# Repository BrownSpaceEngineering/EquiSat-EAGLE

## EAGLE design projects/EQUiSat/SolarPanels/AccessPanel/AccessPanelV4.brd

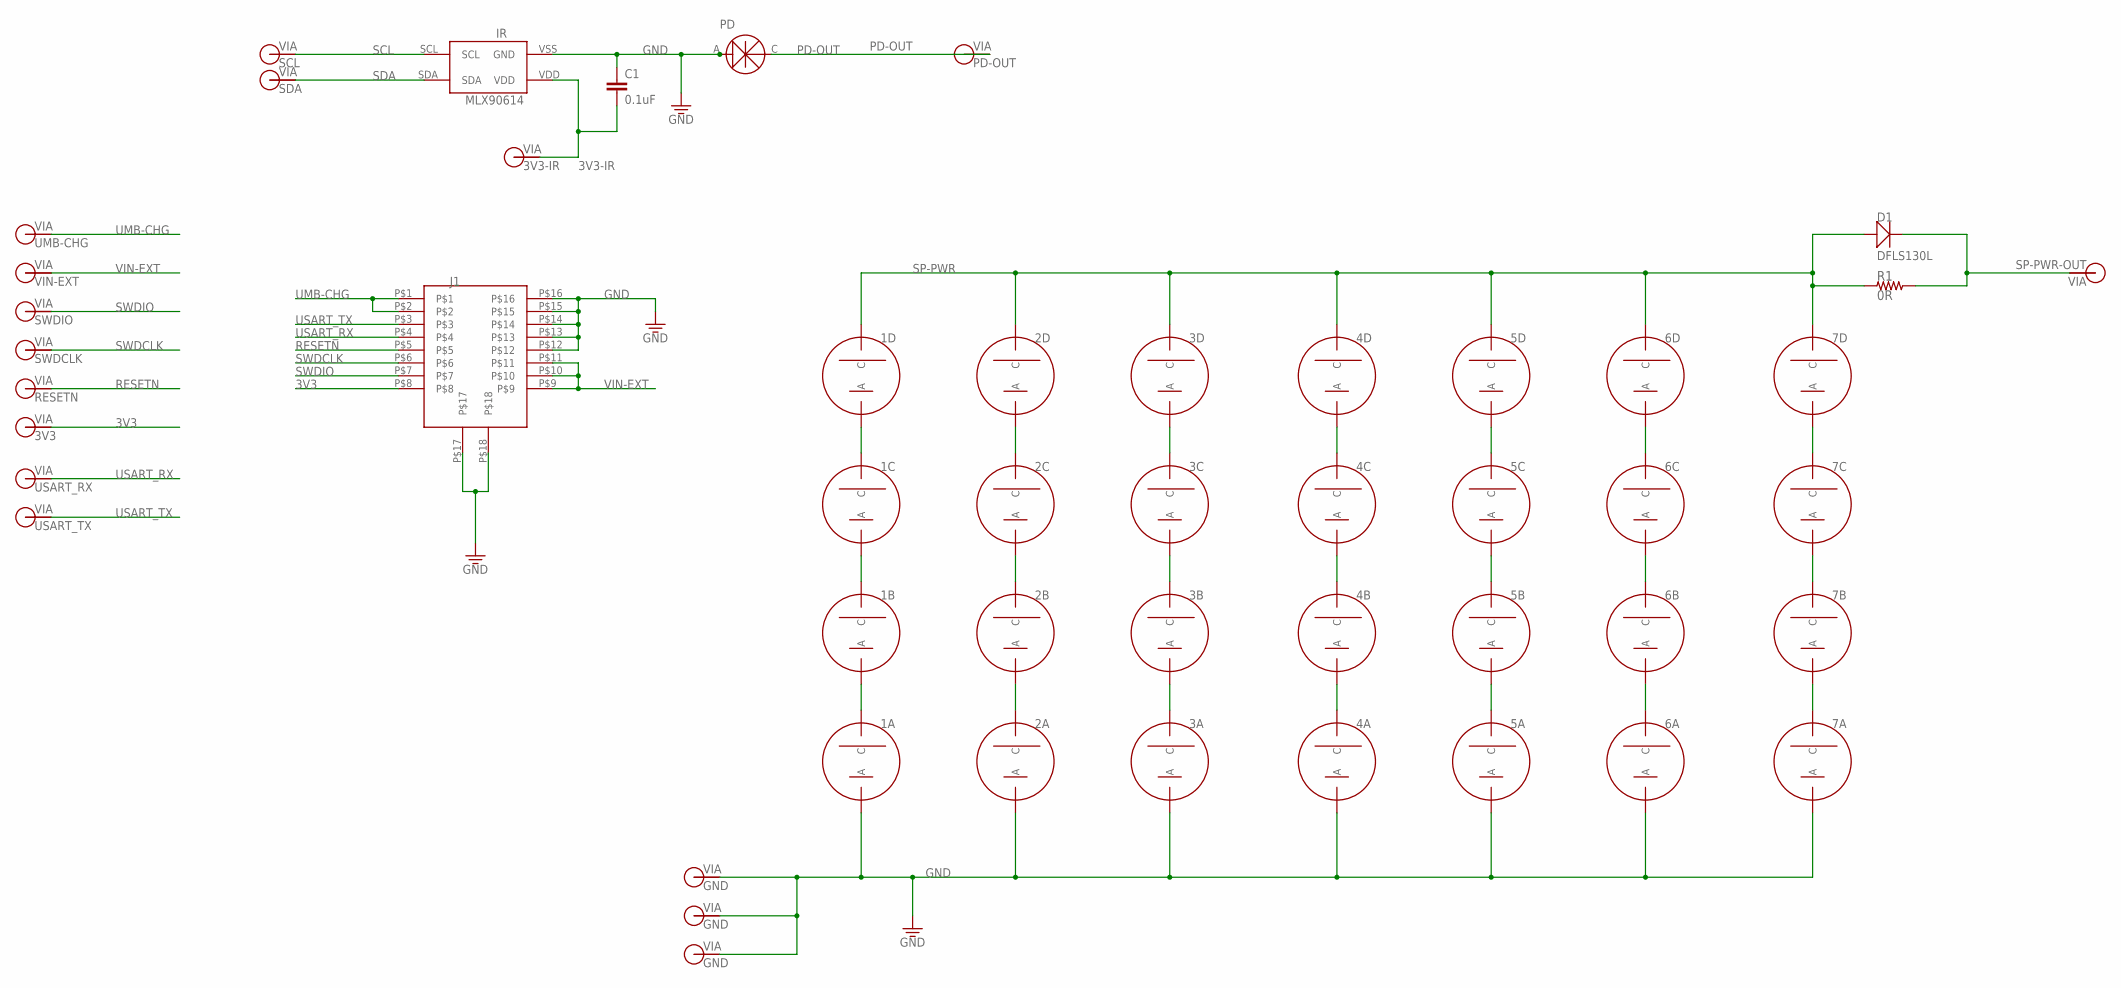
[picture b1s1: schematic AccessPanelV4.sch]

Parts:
1A, 1B, 1C, 1D, 2A, 2B, 2C, 2D, 3A, 3B, 3C, 3D, 4A, 4B, 4C, 4D, 5A, 5B, 5C, 5D, 6A, 6B, 6C, 6D, 7A, 7B, 7C, 7D: SOLARCELLV3; TRISOLX-V3
C1: 0.1uF; 0805
D1: DFLS130L; PWRDI-123
IR: MXL90614; MXL90620
J1: FFC-16; 68611614422
PD: TEMD6200
R1: 0R; 1210
SCL: SCL; VIA-60MIL
SDA: SDA; VIA-60MIL
V1: SP-PWR-OUT; VIA-60MIL
V2, V4, V5: GND; VIA-60MIL
V3: 3V3-IR; VIA-60MIL
V6: PD-OUT; VIA-60MIL
V7: UMB-CHG; VIA-60MIL
V8: VIN-EXT; VIA-60MIL
V9: SWDIO; VIA-60MIL
V10: SWDCLK; VIA-60MIL
V11: RESETN; VIA-60MIL
V14: USART_RX; VIA-60MIL
V15: USART_TX; VIA-60MIL
V16: 3V3; VIA-60MIL

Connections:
3V3: J1.P$8, V16.P$1
3V3-IR: C1.2, IR.VDD, V3.P$1
GND: 1A.ANODE (A), 2A.ANODE (A), 3A.ANODE (A), 4A.ANODE (A), 5A.ANODE (A), 6A.ANODE (A), 7A.ANODE (A), C1.1, IR.VSS (GND), J1.P$12, J1.P$13, J1.P$14, J1.P$15, J1.P$16, J1.P$17, J1.P$18, PD.A, V2.P$1, V4.P$1, V5.P$1
unnamed: 1C.CATHODE (C), 1D.ANODE (A)
unnamed: 2C.CATHODE (C), 2D.ANODE (A)
unnamed: 3C.CATHODE (C), 3D.ANODE (A)
unnamed: 4C.CATHODE (C), 4D.ANODE (A)
unnamed: 5C.CATHODE (C), 5D.ANODE (A)
unnamed: 1A.CATHODE (C), 1B.ANODE (A)
unnamed: 2A.CATHODE (C), 2B.ANODE (A)
unnamed: 3A.CATHODE (C), 3B.ANODE (A)
unnamed: 4A.CATHODE (C), 4B.ANODE (A)
unnamed: 5A.CATHODE (C), 5B.ANODE (A)
unnamed: 1B.CATHODE (C), 1C.ANODE (A)
unnamed: 2B.CATHODE (C), 2C.ANODE (A)
unnamed: 3B.CATHODE (C), 3C.ANODE (A)
unnamed: 4B.CATHODE (C), 4C.ANODE (A)
unnamed: 5B.CATHODE (C), 5C.ANODE (A)
unnamed: 6C.CATHODE (C), 6D.ANODE (A)
unnamed: 6A.CATHODE (C), 6B.ANODE (A)
unnamed: 6B.CATHODE (C), 6C.ANODE (A)
unnamed: 7C.CATHODE (C), 7D.ANODE (A)
unnamed: 7A.CATHODE (C), 7B.ANODE (A)
unnamed: 7B.CATHODE (C), 7C.ANODE (A)
PD-OUT: PD.C, V6.P$1
RESETN: J1.P$5, V11.P$1
SCL: IR.SCL, SCL.P$1
SDA: IR.SDA, SDA.P$1
SP-PWR: 1D.CATHODE (C), 2D.CATHODE (C), 3D.CATHODE (C), 4D.CATHODE (C), 5D.CATHODE (C), 6D.CATHODE (C), 7D.CATHODE (C), D1.A, R1.P$1 (1)
SP-PWR-OUT: D1.C, R1.P$2 (2), V1.P$1
SWDCLK: J1.P$6, V10.P$1
SWDIO: J1.P$7, V9.P$1
UMB-CHG: J1.P$1, J1.P$2, V7.P$1
USART_RX: J1.P$4, V14.P$1
USART_TX: J1.P$3, V15.P$1
VIN-EXT: J1.P$9, J1.P$10, J1.P$11, V8.P$1

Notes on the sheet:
GND
PD-OUT

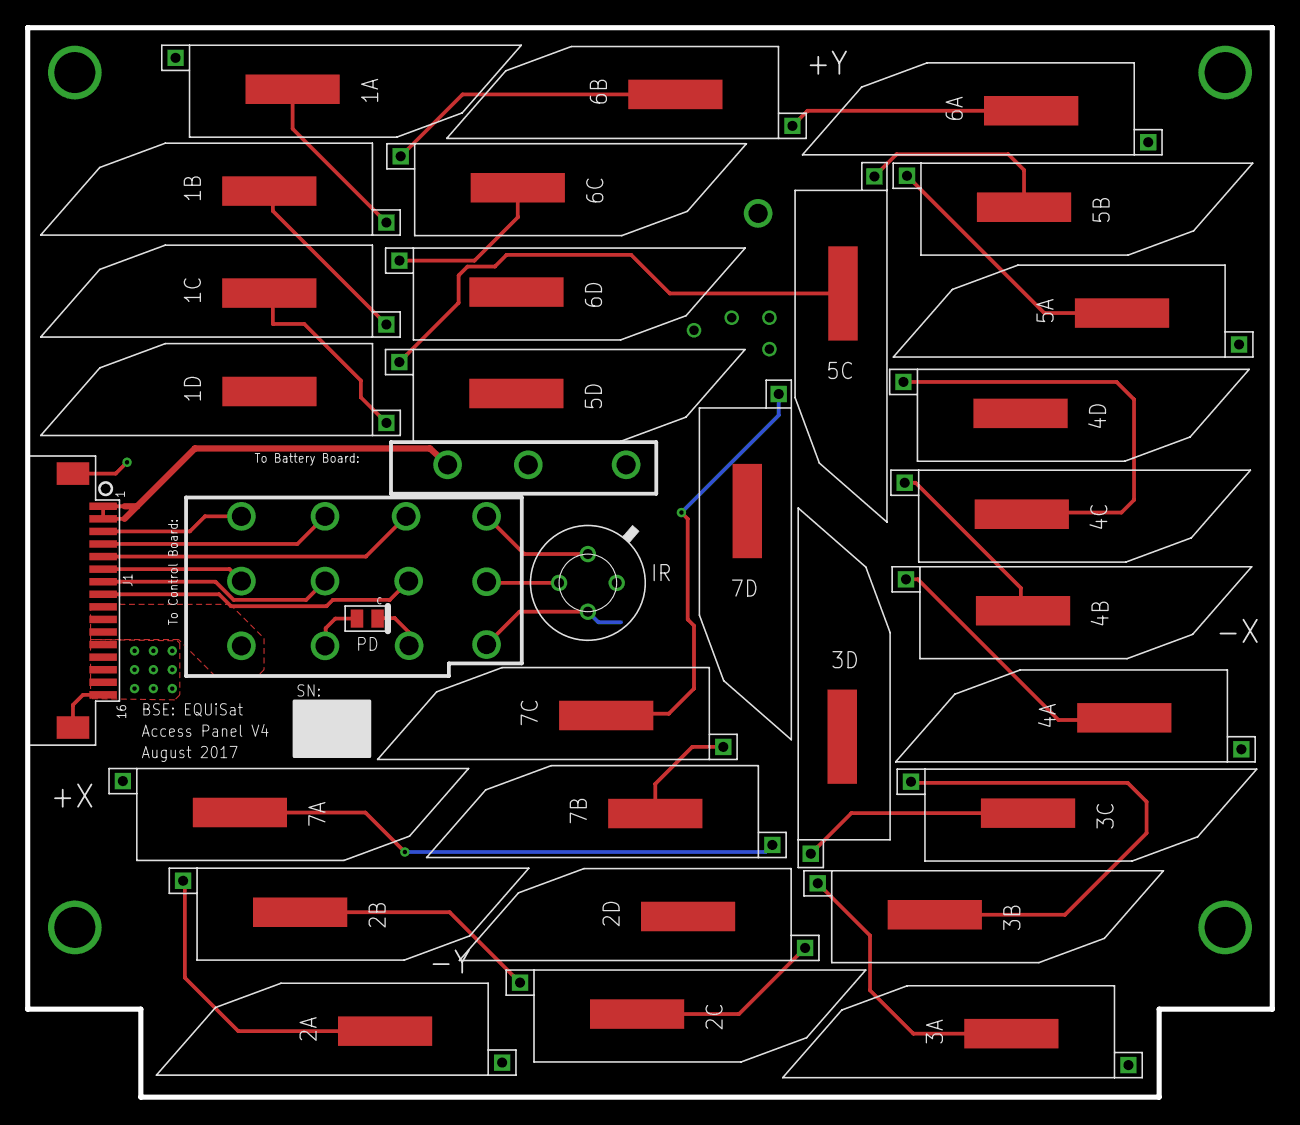
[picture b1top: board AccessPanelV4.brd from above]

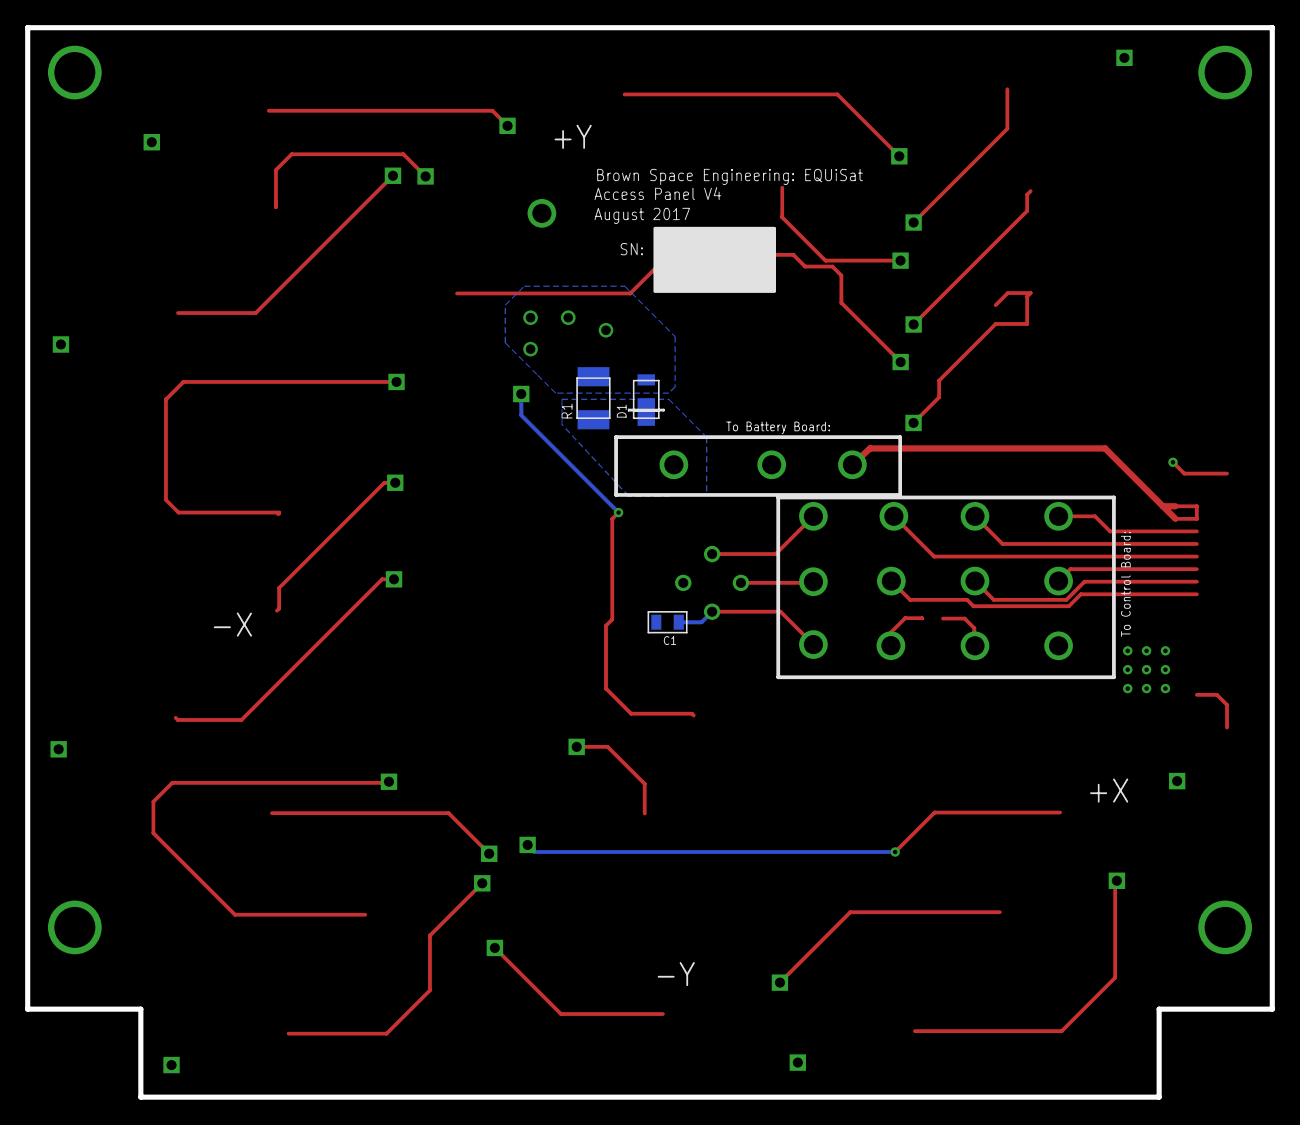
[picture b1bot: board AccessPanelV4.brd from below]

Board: 2 copper layers, 99.0 x 85.1 mm, 50 parts (3 on the bottom side), 36 nets.

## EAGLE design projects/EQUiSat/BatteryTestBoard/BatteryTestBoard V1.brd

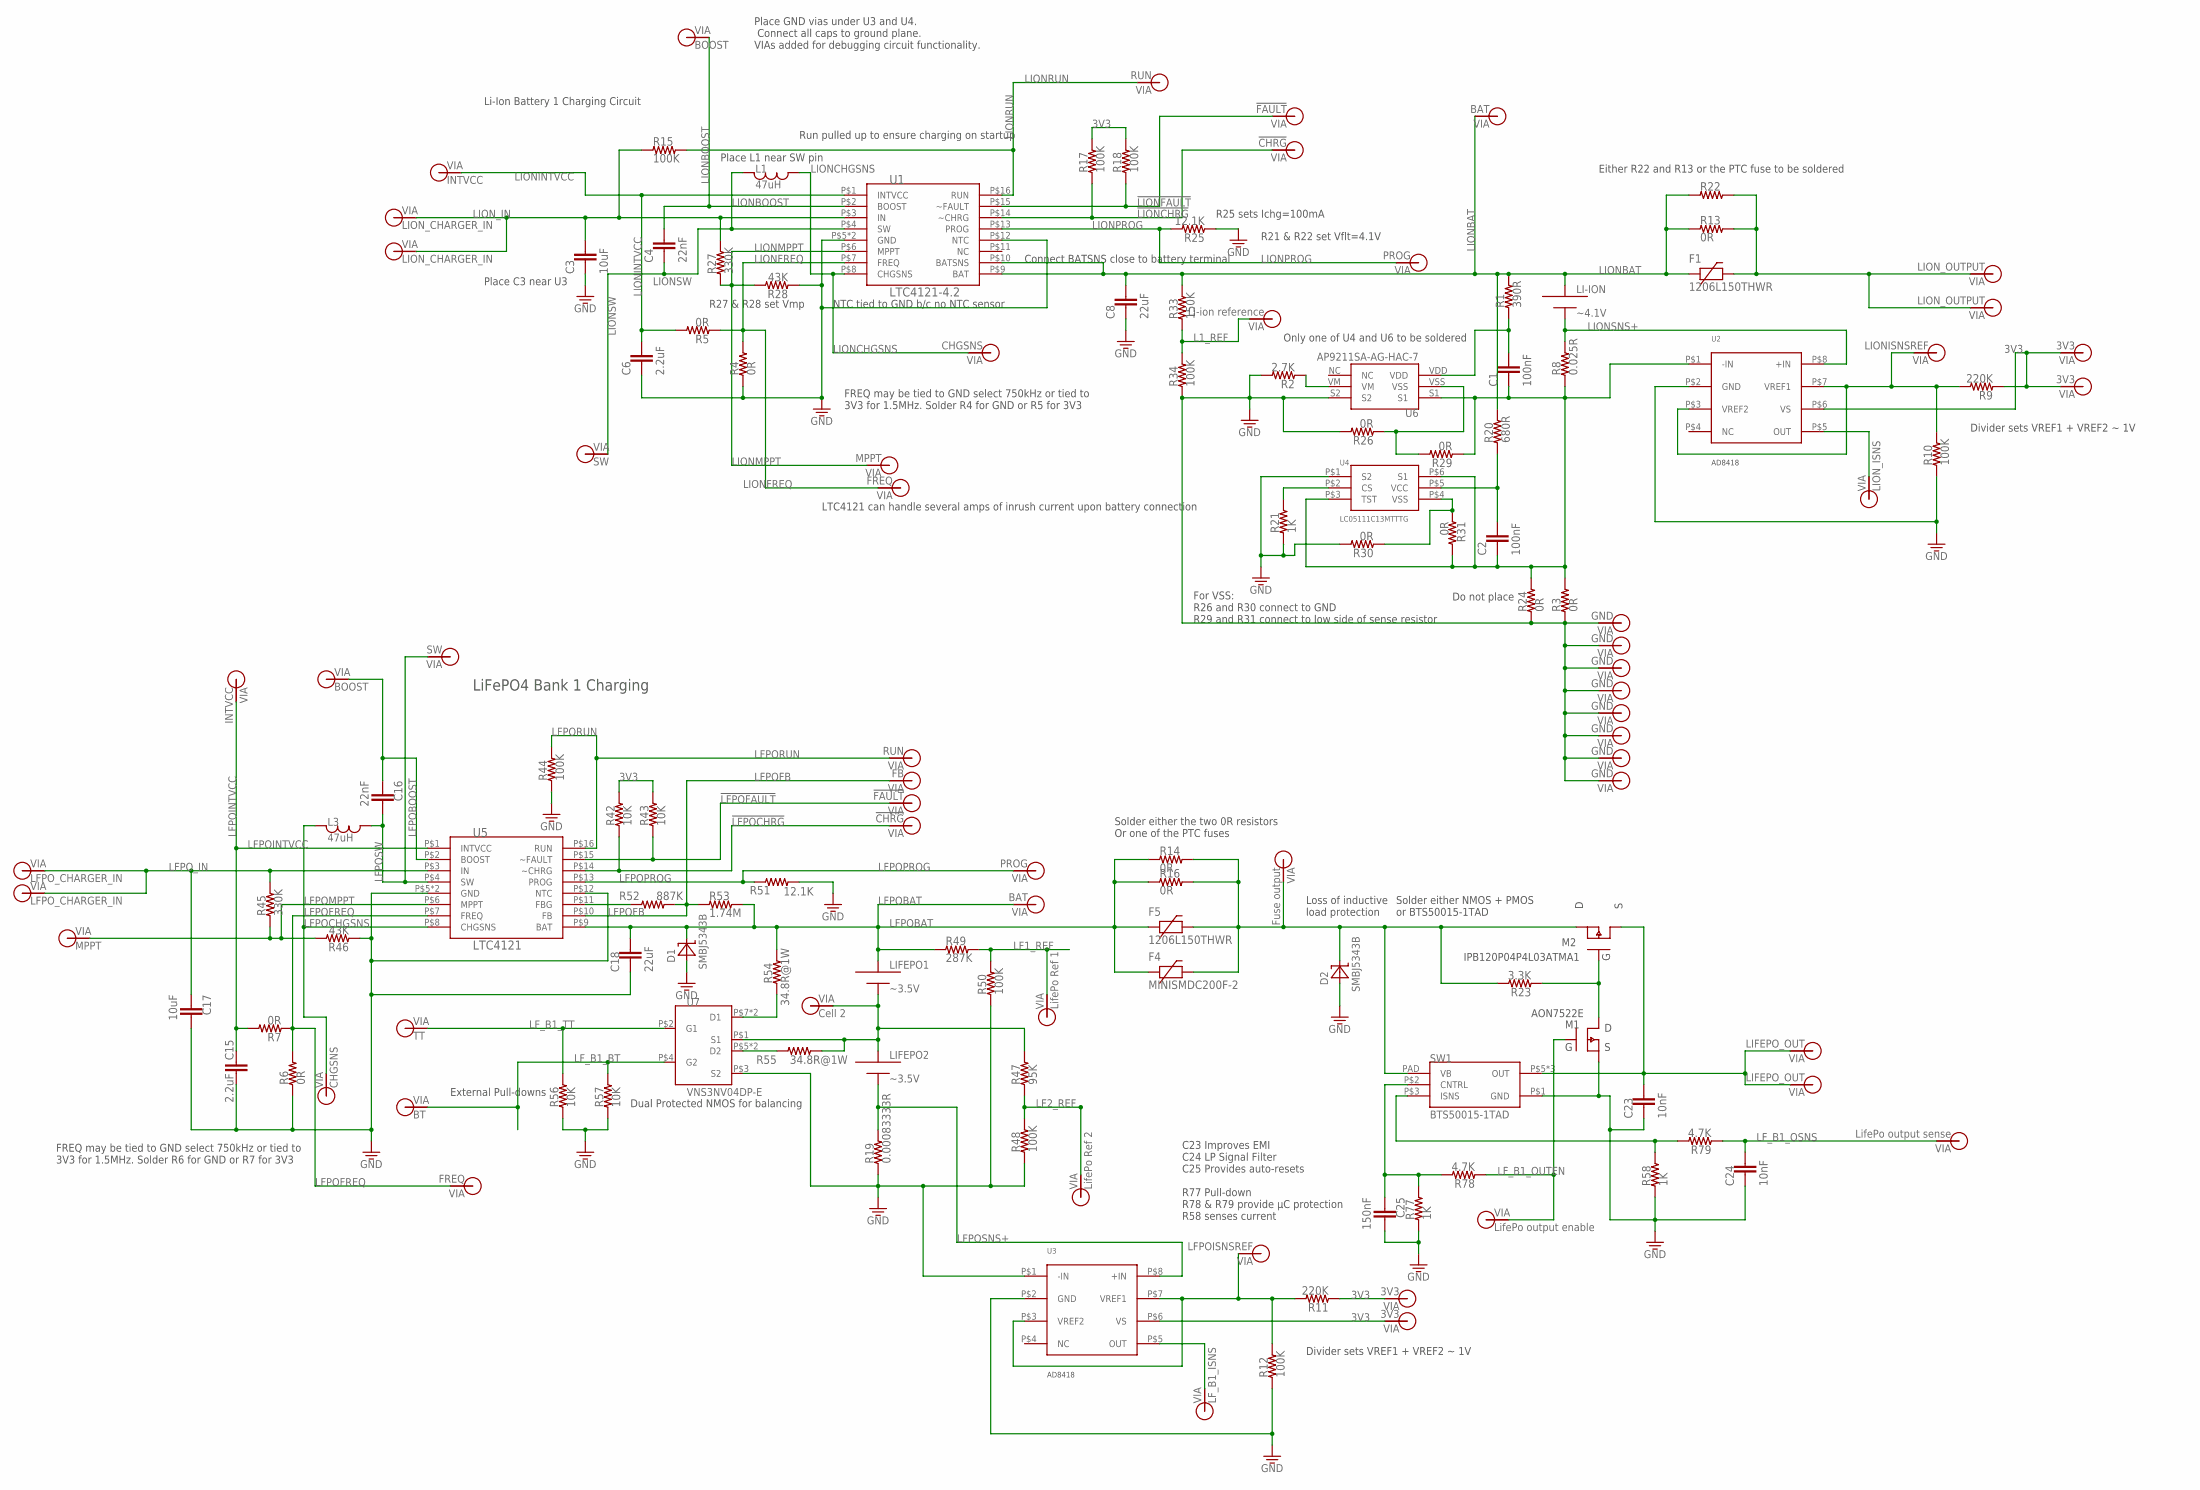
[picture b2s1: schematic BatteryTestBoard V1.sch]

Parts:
C1, C2: 100nF; 0805
C3, C17: 10uF; 0805
C4, C16: 22nF; 0805
C6, C15: 2.2uF; 0805
C8, C18: 22uF; 0805
C23, C24: 10nF; 0805
C25: 150nF; 0805
D1, D2: SMBJ5343B; DO214AA
F1, F5: 1206L150THWR; 1206
F4: MINISMDC200F-2; 1812
L1, L3: 47uH; 1812
LI-ION: ~4.1V; EQUISAT-BATTERY-VA
LIFEPO1, LIFEPO2: ~3.5V; EQUISAT-BATTERY-VA
M1: AON7522E; DFN-3X3-8
M2: IPB120P04P4L03ATMA1; TO263
R1: 390R; 0805
R2: 2.7K; 0805
R3, R13, R14, R16, R22, R24: 0R; 1210
R4, R5, R6, R7, R26, R29, R30, R31: 0R; 0805
R8: 0.025R; 1210
R9, R11: 220K; 0805
R10, R12, R15, R17, R18, R34, R44, R48, R50: 100K; 0805
R19: 0.00083333R; 1210
R20: 680R; 0805
R21, R58, R77: 1K; 0805
R23: 3.3K; 0805
R25, R51: 12.1K; 0805
R27, R45: 330K; 0805
R28, R46: 43K; 0805
R33: 150K; 0805
R42, R43, R56, R57: 10K; 0805
R47: 95K; 0805
R49: 287K; 0805
R52: 887K; 0805
R53: 1.74M; 0805
R54, R55: 34.8R@1W; 1210
R78, R79: 4.7K; 0805
SW1: BTS50015-1TAD; TO-263-7-8
U1: LTC4121-4.2; QFN-16-PAD
U2, U3: AD8418; MSOP-8
U4: LC05111C13MTTTG; WDFN6
U5: LTC4121; QFN-16-PAD
U6: AP9211SA-AG-HAC-7; U-DFN2030-6
U7: VNS3NV04DP-E; SO-8
V1, V37: LION_OUTPUT; VIA-120MIL
V2: Fuse output; VIA-60MIL-SQ
V3, V4, V5, V6, V7, V8, V10, V41: GND; VIA-60MIL-SQ
V9, V75: LFPO_CHARGER_IN; VIA-60MIL-SQ
V11: LFPOISNSREF; VIA-60MIL-SQ
V12: LIONISNSREF; VIA-60MIL-SQ
V13: LF_B1_ISNS; VIA-60MIL-SQ
V16: Cell 2; VIA-60MIL-SQ
V20: LifePo output enable; VIA-60MIL-SQ
V21, V26: LIFEPO_OUT; VIA-120MIL
V29: TT; VIA-60MIL-SQ
V31: LifePo output sense; VIA-60MIL-SQ
V32: BT; VIA-60MIL-SQ
V34, V35: LION_CHARGER_IN; VIA-60MIL-SQ
V36, V54: BOOST; VIA-60MIL-SQ
V38, V57: SW; VIA-60MIL-SQ
V39, V60: MPPT; VIA-60MIL-SQ
V43: LION_ISNS; VIA-60MIL-SQ
V44: Li-ion reference; VIA-60MIL-SQ
V46, V61: CHGSNS; VIA-60MIL-SQ
V47, V62: FREQ; VIA-60MIL-SQ
V48, V63: BAT; VIA-60MIL-SQ
V50, V65: PROG; VIA-60MIL-SQ
V51, V66: !CHRG; VIA-60MIL-SQ
V52, V67: !FAULT; VIA-60MIL-SQ
V53, V68: RUN; VIA-60MIL-SQ
V55, V69: INTVCC; VIA-60MIL-SQ
V58: LifePo Ref 1; VIA-60MIL-SQ
V59: LifePo Ref 2; VIA-60MIL-SQ
V70: FB; VIA-60MIL-SQ
V71, V72, V73, V74: 3V3; VIA-60MIL-SQ

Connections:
3V3: R9.1, R11.1, R17.2, R18.2, R42.2, R43.2, U2.P$6 (VS), U3.P$6 (VS), V71.P$1, V72.P$1, V73.P$1, V74.P$1
!LFPOCHRG: R42.1, U5.P$14 (~CHRG), V66.P$1
!LFPOFAULT: R43.1, U5.P$15 (~FAULT), V67.P$1
!LIONCHRG: R17.1, U1.P$14 (~CHRG), V51.P$1
!LIONFAULT: R18.1, U1.P$15 (~FAULT), V52.P$1
FUSE_OUT: D2.C, F4.P$2, F5.2, M2.2 (D), R14.P$2 (2), R16.P$2 (2), R23.2, SW1.PAD (VB), V2.P$1
GND: C3.2, C6.2, C8.2, C15.1, C17.1, C18.2, C23.2, C24.2, C25.1, D1.A, D2.A, M1.P$1 (S), M1.P$2 (S), M1.P$3 (S), R2.2, R3.P$1 (1), R4.1, R6.1, R10.1, R12.1, R19.P$1 (1), R21.1, R24.P$1 (1), R25.1, R26.2, R28.1, R30.2, R34.1, R44.1, R46.1, R48.1, R50.1, R51.2, R56.1, R57.1, R58.1, R77.1, SW1.P$1 (GND), U1.P$5 (GND), U1.P$12 (NTC), U1.P$17 (GND), U2.P$2 (GND), U3.P$1 (-IN), U3.P$2 (GND), U4.P$1 (S2), U5.P$5 (GND), U5.P$12 (NTC), U5.P$17 (GND), U6.S2, U7.P$3 (S2), V3.P$1, V4.P$1, V5.P$1, V6.P$1, V7.P$1, V8.P$1, V10.P$1, V41.P$1
L1_REF: R33.1, R34.2, V44.P$1
L1_SNS: U2.P$5 (OUT), V43.P$1
L1_SNS1: U3.P$5 (OUT), V13.P$1
LF1_REF: R49.2, R50.2, V58.P$1
LF2_REF: R47.1, R48.2, V59.P$1
LFPOBAT: C18.1, D1.C, F4.P$1, F5.1, LIFEPO1.PLUS, R14.P$1 (1), R16.P$1 (1), R49.1, R53.2, R54.P$2 (2), U5.P$9 (BAT), V63.P$1
LFPOBOOST: C16.2, U5.P$2 (BOOST), V54.P$1
LFPOCHGSNS: L3.P$1, U5.P$8 (CHGSNS), V61.P$1
LFPOFB: R52.2, R53.1, U5.P$10 (FB), V70.P$1
LFPOFREQ: R6.2, R7.1, U5.P$7 (FREQ), V62.P$1
LFPOINTVCC: C15.2, R7.2, U5.P$1 (INTVCC), V69.P$1
LFPOMPPT: R45.1, R46.2, U5.P$6 (MPPT), V60.P$1
LFPOPROG: R51.1, U5.P$13 (PROG), V65.P$1
LFPORUN: R44.2, U5.P$16 (RUN), V68.P$1
LFPOSNS+: LIFEPO2.MINUS, R19.P$2 (2), U3.P$8 (+IN)
LFPOSW: C16.1, L3.P$2, U5.P$4 (SW), V57.P$1
LFPO_IN: C17.2, R45.2, U5.P$3 (IN), V9.P$1, V75.P$1
LF_B1_BT: R57.2, U7.P$4 (G2), V32.P$1
LF_B1_OSNS: C24.1, R79.1, V31.P$1
LF_B1_OUTEN: M1.P$4 (G), R78.1, V20.P$1
LF_B1_TT: R56.2, U7.P$2 (G1), V29.P$1
LIFE2: LIFEPO1.MINUS, LIFEPO2.PLUS, R47.2, R55.P$1 (1), U7.P$1 (S1), V16.P$1
LIONBAT: C8.1, F1.1, LI-ION.PLUS, R1.2, R13.P$1 (1), R20.2, R22.P$1 (1), R33.2, U1.P$9 (BAT), U1.P$10 (BATSNS), V48.P$1
LIONBOOST: C4.1, U1.P$2 (BOOST), V36.P$1
LIONCHGSNS: L1.P$2, U1.P$8 (CHGSNS), V46.P$1
LIONFREQ: R4.2, R5.1, U1.P$7 (FREQ), V47.P$1
LIONINTVCC: C6.1, R5.2, U1.P$1 (INTVCC), V55.P$1
LIONMPPT: R27.1, R28.2, U1.P$6 (MPPT), V39.P$1
LIONPROG: R25.2, U1.P$13 (PROG), V50.P$1
LIONRUN: R15.2, U1.P$16 (RUN), V53.P$1
LIONSNS+: LI-ION.MINUS, R8.P$2 (2), U2.P$8 (+IN)
LIONSW: C4.2, L1.P$1, U1.P$4 (SW), V38.P$1
LION_IN: C3.1, R15.1, R27.2, U1.P$3 (IN), V34.P$1, V35.P$1
LPFOFBG: R52.1, U5.P$11 (FBG)
unnamed: R2.1, U6.VM
unnamed: R11.2, R12.2, U3.P$3 (VREF2), U3.P$7 (VREF1), V11.P$1
unnamed: F1.2, R13.P$2 (2), R22.P$2 (2), V1.P$1, V37.P$1
unnamed: R26.1, R29.2, U6.VSS
unnamed: C1.1, R1.1, U6.VDD
unnamed: C23.1, M2.3 (S), SW1.P$5 (OUT), SW1.P$6 (OUT), SW1.P$7 (OUT), V21.P$1, V26.P$1
unnamed: M1.P$5 (D), M1.P$6 (D), M1.P$7 (D), M1.P$8 (D), M1.PAD (D), M2.1 (G), R23.1
unnamed: C2.1, R20.1, U4.P$5 (VCC)
unnamed: C1.2, C2.2, R3.P$2 (2), R8.P$1 (1), R24.P$2 (2), R29.1, R31.2, U2.P$1 (-IN), U4.P$3 (TST), U4.P$6 (S1), U6.S1
unnamed: R30.1, R31.1, U4.P$4 (VSS)
unnamed: R9.2, R10.2, U2.P$3 (VREF2), U2.P$7 (VREF1), V12.P$1
unnamed: R21.2, U4.P$2 (CS)
unnamed: R54.P$1 (1), U7.P$7 (D1), U7.P$8 (D1)
unnamed: R55.P$2 (2), U7.P$5 (D2), U7.P$6 (D2)
unnamed: C25.2, R77.2, R78.2, SW1.P$2 (CNTRL)
unnamed: R58.2, R79.2, SW1.P$3 (ISNS)

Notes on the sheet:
FREQ may be tied to GND select 750kHz or tied to 3V3 for 1.5MHz. Solder R4 for GND or R5 for 3V3
R25 sets Ichg=100mA
R21 & R22 set Vflt=4.1V
R27 & R28 set Vmp
Place C3 near U3
Place L1 near SW pin
Place GND vias under U3 and U4. Connect all caps to ground plane. VIAs added for debugging circuit functionality.
Li-Ion Battery 1 Charging Circuit
Run pulled up to ensure charging on startup
NTC tied to GND b/c no NTC sensor
LTC4121 can handle several amps of inrush current upon battery connection
LiFePO4 Bank 1 Charging
External Pull-downs
Dual Protected NMOS for balancing
Solder either the two 0R resistors Or one of the PTC fuses
C23 Improves EMI C24 LP Signal Filter C25 Provides auto-resets R77 Pull-down R78 & R79 provide µC protection R58 senses current
Divider sets VREF1 + VREF2 ~ 1V
Do not place
Only one of U4 and U6 to be soldered
Either R22 and R13 or the PTC fuse to be soldered
Connect BATSNS close to battery terminal
AON7522E
Solder either NMOS + PMOS or BTS50015-1TAD
Loss of inductive load protection
FREQ may be tied to GND select 750kHz or tied to 3V3 for 1.5MHz. Solder R6 for GND or R7 for 3V3
For VSS: R26 and R30 connect to GND R29 and R31 connect to low side of sense resistor

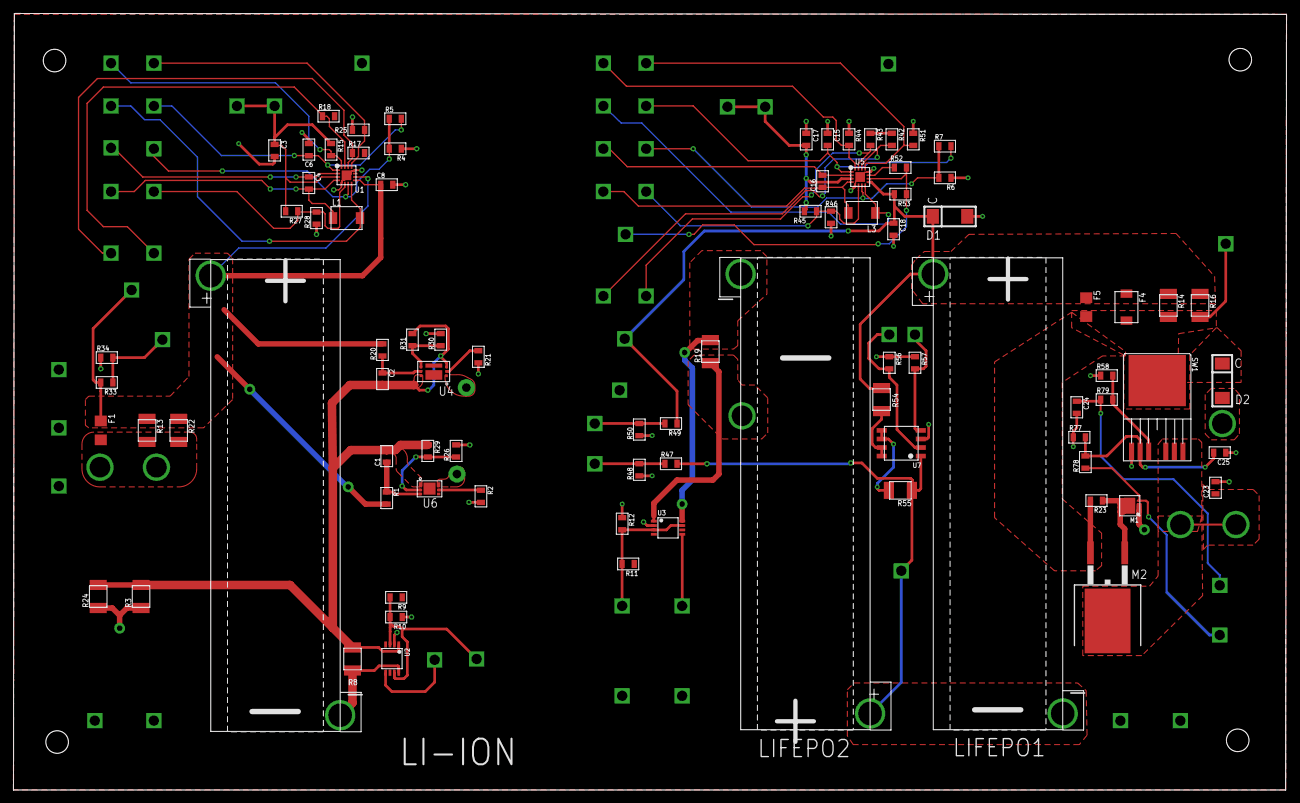
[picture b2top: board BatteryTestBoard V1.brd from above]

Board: 2 copper layers, 188.8 x 115.2 mm, 142 parts (0 on the bottom side), 57 nets.

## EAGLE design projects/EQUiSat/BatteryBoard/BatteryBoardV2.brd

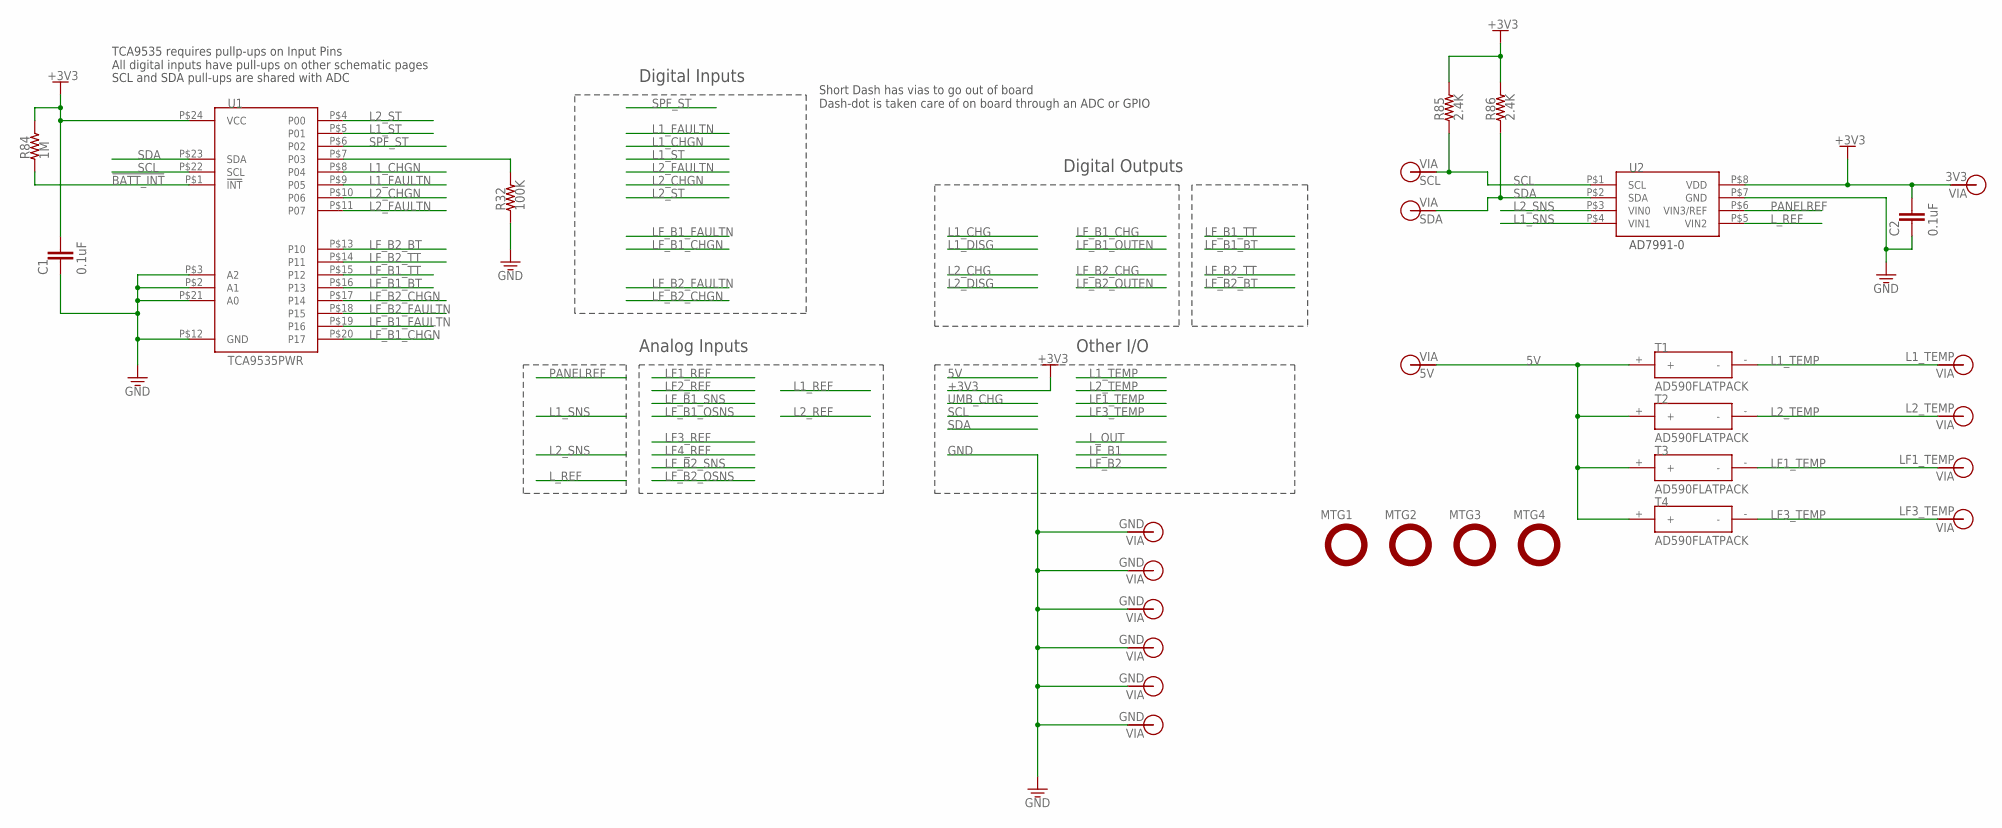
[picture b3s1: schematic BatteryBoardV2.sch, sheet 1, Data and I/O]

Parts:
C1, C2: 0.1uF; 0805
MTG1, MTG2, MTG3, MTG4: MTG-NPTH-#2-CLOSE; #2-CLOSE-NPTH
R32: 100K; 0805
R84: 1M; 0805
R85, R86: 2.4K; 0805
T1, T2, T3, T4: AD590FLATPACK; FLATPACK
U1: TCA9535PWR; TSSOP-24
U2: AD7991-0; SOT-23-8
V1, V2, V4: GND; VIA-120MIL
V3, V28, V36: GND; VIA-60MIL-SQ
V5: SCL; VIA-60MIL
V6: SDA; VIA-60MIL
V7: 5V; VIA-60MIL
V8: L1_TEMP; VIA-60MIL
V9: L2_TEMP; VIA-60MIL
V10: LF1_TEMP; VIA-60MIL
V11: LF3_TEMP; VIA-60MIL
V12: 3V3; VIA-60MIL

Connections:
5V: T1.+, T2.+, T3.+, T4.+, V7.P$1
!BATT_INT!: R84.1, U1.P$1 (!INT!)
+3V3: C1.1, C2.1, R84.2, R85.2, R86.2, U1.P$24 (VCC), U2.P$8 (VDD), V12.P$1; also elsewhere on the board
GND: C1.2, C2.2, R32.1, U1.P$2 (A1), U1.P$3 (A2), U1.P$12 (GND), U1.P$21 (A0), U2.P$7 (GND), V1.P$1, V2.P$1, V3.P$1, V4.P$1, V28.P$1, V36.P$1; also elsewhere on the board
L1_CHGN: U1.P$8 (P04); also elsewhere on the board
L1_FAULTN: U1.P$9 (P05); also elsewhere on the board
L1_SNS: U2.P$4 (VIN1); also elsewhere on the board
L1_ST: U1.P$5 (P01); also elsewhere on the board
L1_TEMP: T1.-, V8.P$1
L2_CHGN: U1.P$10 (P06); also elsewhere on the board
L2_FAULTN: U1.P$11 (P07); also elsewhere on the board
L2_SNS: U2.P$3 (VIN0); also elsewhere on the board
L2_ST: U1.P$4 (P00); also elsewhere on the board
L2_TEMP: T2.-, V9.P$1
LF1_TEMP: T3.-, V10.P$1
LF3_TEMP: T4.-, V11.P$1
LF_B1_BT: U1.P$16 (P13); also elsewhere on the board
LF_B1_CHGN: U1.P$20 (P17); also elsewhere on the board
LF_B1_FAULTN: U1.P$19 (P16); also elsewhere on the board
LF_B1_TT: U1.P$15 (P12); also elsewhere on the board
LF_B2_BT: U1.P$13 (P10); also elsewhere on the board
LF_B2_CHGN: U1.P$17 (P14); also elsewhere on the board
LF_B2_FAULTN: U1.P$18 (P15); also elsewhere on the board
LF_B2_TT: U1.P$14 (P11); also elsewhere on the board
L_REF: U2.P$5 (VIN2); also elsewhere on the board
unnamed: R32.2, U1.P$7 (P03)
PANELREF: U2.P$6 (VIN3/REF); also elsewhere on the board
SCL: R85.1, U1.P$22 (SCL), U2.P$1 (SCL), V5.P$1
SDA: R86.1, U1.P$23 (SDA), U2.P$2 (SDA), V6.P$1
SPF_ST: U1.P$6 (P02); also elsewhere on the board

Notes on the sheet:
Digital Inputs
Digital Outputs
Analog Inputs
Other I/O
Short Dash has vias to go out of board Dash-dot is taken care of on board through an ADC or GPIO
SCL and SDA pull-ups are shared with ADC
TCA9535 requires pullp-ups on Input Pins All digital inputs have pull-ups on other schematic pages

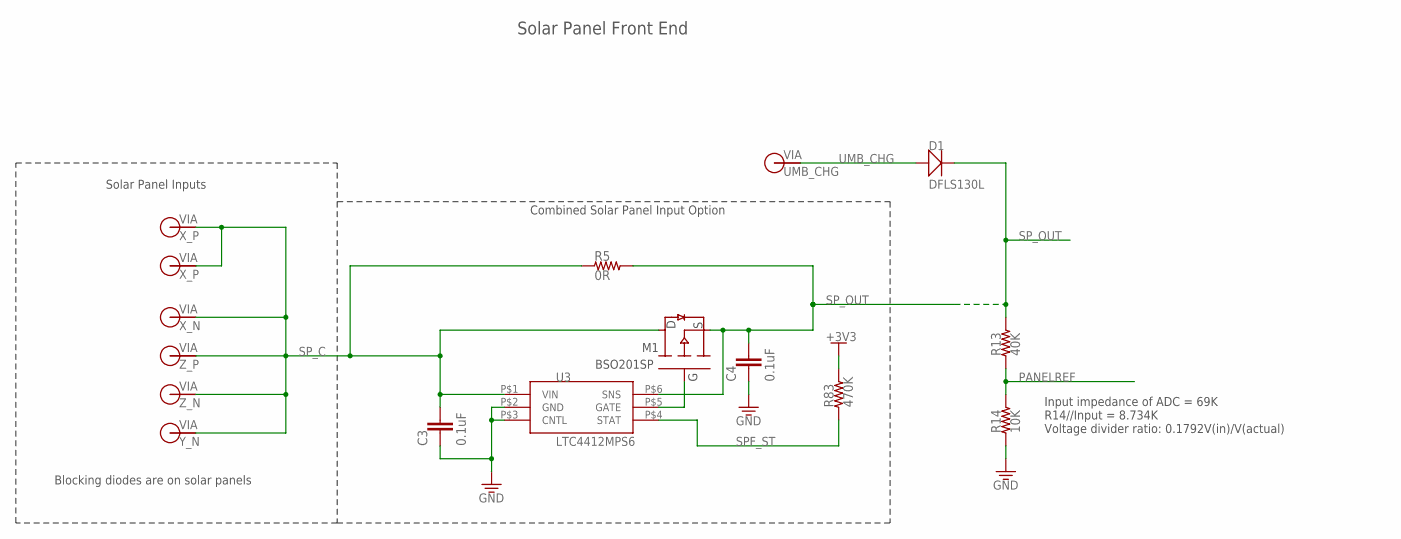
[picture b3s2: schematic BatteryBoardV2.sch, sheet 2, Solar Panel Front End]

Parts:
C3, C4: 0.1uF; 0805
D1: DFLS130L; PWRDI-123
M1: BSO201SP; SO-8
R5: 0R; 0805
R13: 40K; 0805
R14: 10K; 0805
R83: 470K; 0805
U3: LTC4412MPS6; TSOT23-6
V13: X_P; VIA-60MIL
V14: X_P; VIA-60MIL-SQ
V15: X_N; VIA-60MIL
V16: Z_P; VIA-60MIL
V17: Z_N; VIA-60MIL
V18: Y_N; VIA-60MIL
V19: UMB_CHG; VIA-60MIL

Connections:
+3V3: R83.2; also elsewhere on the board
GND: C3.2, C4.2, R14.1, U3.P$2 (GND), U3.P$3 (CNTL); also elsewhere on the board
unnamed: M1.P$4 (G), U3.P$5 (GATE)
PANELREF: R13.1, R14.2; also elsewhere on the board
SPF_ST: R83.1, U3.P$4 (STAT); also elsewhere on the board
SP_C: C3.1, M1.P$5 (D), M1.P$6 (D), M1.P$7 (D), M1.P$8 (D), R5.1, U3.P$1 (VIN), V13.P$1, V14.P$1, V15.P$1, V16.P$1, V17.P$1, V18.P$1
SP_OUT: C4.1, D1.C, M1.P$1 (S), M1.P$2 (S), M1.P$3 (S), R5.2, R13.2, U3.P$6 (SNS); also elsewhere on the board
UMB_CHG: D1.A, V19.P$1

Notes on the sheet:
Solar Panel Inputs
Combined Solar Panel Input Option
Solar Panel Front End
Blocking diodes are on solar panels
Input impedance of ADC = 69K R14//Input = 8.734K Voltage divider ratio: 0.1792V(in)/V(actual)
